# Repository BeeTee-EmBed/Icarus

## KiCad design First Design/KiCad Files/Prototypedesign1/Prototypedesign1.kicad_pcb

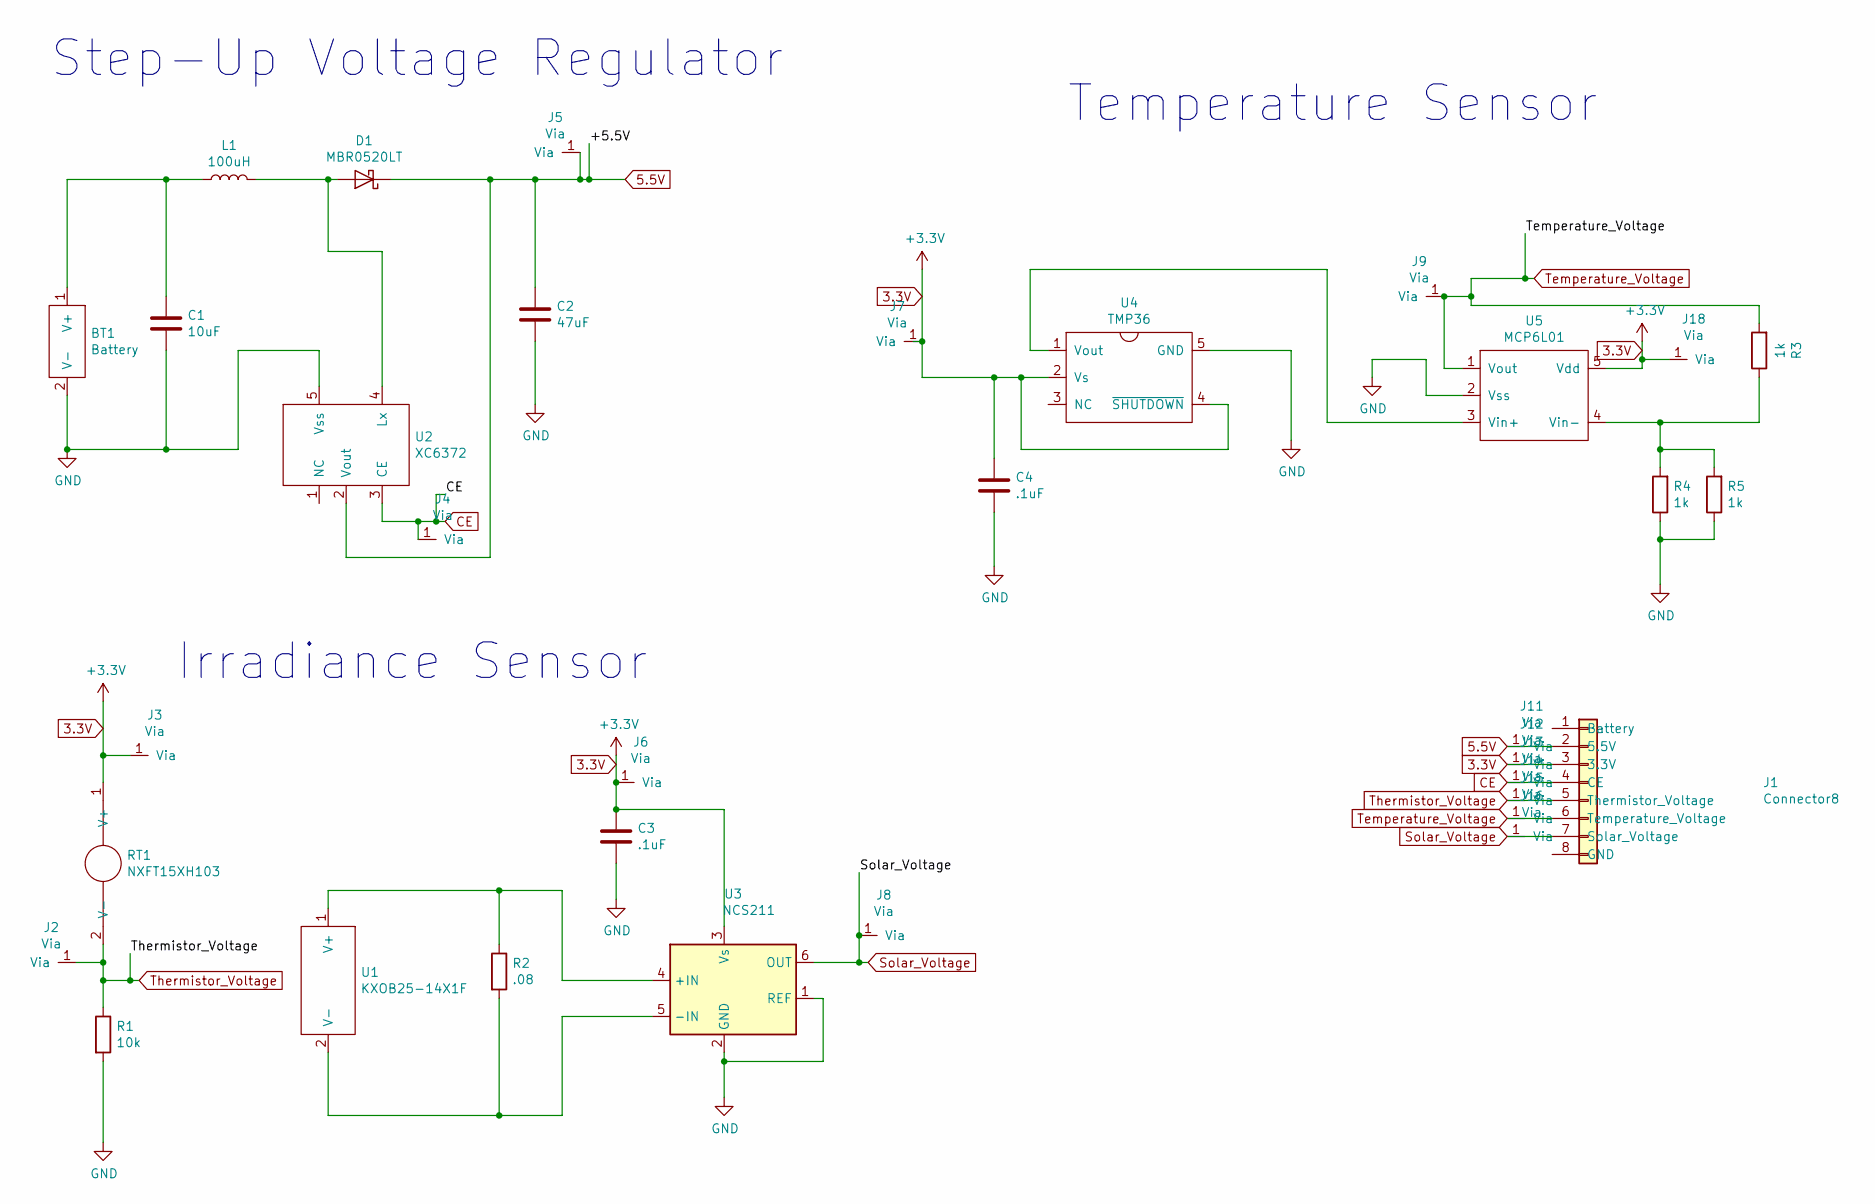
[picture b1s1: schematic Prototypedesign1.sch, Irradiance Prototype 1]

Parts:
BT1: Battery; Prototypebatteryholder
C1: 10uF; C_0603_1608Metric_Pad1.05x0.95mm_HandSolder
C2: 47uF; C_1210_3225Metric_Pad1.42x2.65mm_HandSolder
C3, C4: .1uF; C_0805_2012Metric_Pad1.15x1.40mm_HandSolder
D1: MBR0520LT; D_SOD-123
J1: Connector8; SIP-8
J2, J3, J4, J5, J6, J7, J8, J9, J11, J12, J13, J14, J15, J16, J18: Via
L1: 100uH; Inductor100uH
R1: 10k; R_0805_2012Metric_Pad1.15x1.40mm_HandSolder
R2: .08; R_2512_6332Metric_Pad1.52x3.35mm_HandSolder
R3, R4, R5: 1k; R_0805_2012Metric_Pad1.15x1.40mm_HandSolder
RT1: NXFT15XH103; Thermistor
U1: KXOB25-14X1F; KXOB25
U2: XC6372
U3: NCS211; SOT-363_SC-70-6
U4: TMP36; SOT-23-5_HandSoldering-TMP36
U5: MCP6L01; SOT-23-5_HandSoldering-MCP6L01

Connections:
3.3V: C3.1, C4.1, J1.3 (3.3V), J3.1, J6.1, J7.1, J12.1, J18.1, RT1.1 (V+), U3.3 (Vs), U4.2 (Vs), U4.4 (~SHUTDOWN), U5.5 (Vdd)
5.5V: C2.1, D1.1 (K), J1.2 (5.5V), J5.1, J11.1, U2.2 (Vout)
CE: J1.4 (CE), J4.1, J13.1, U2.3 (CE)
GND: BT1.2 (V-), C1.2, C2.2, C3.2, C4.2, R1.2, R4.1, R5.1, U2.5 (Vss), U3.1 (REF), U3.2 (GND), U4.5 (GND), U5.2 (Vss)
unnamed: BT1.1 (V+), C1.1, L1.1
unnamed: D1.2 (A), L1.2, U2.4 (Lx)
unnamed: R2.1, U1.1 (V+), U3.4 (+IN)
unnamed: R2.2, U1.2 (V-), U3.5 (-IN)
unnamed: R3.1, R4.2, R5.2, U5.4 (Vin-)
unnamed: U4.1 (Vout), U5.3 (Vin+)
Solar_Voltage: J1.7 (Solar_Voltage), J8.1, J16.1, U3.6 (OUT)
Temperature_Voltage: J1.6 (Temperature_Voltage), J9.1, J15.1, R3.2, U5.1 (Vout)
Thermistor_Voltage: J1.5 (Thermistor_Voltage), J2.1, J14.1, R1.1, RT1.2 (V-)

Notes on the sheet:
Step-Up Voltage Regulator
Irradiance Sensor
Temperature Sensor

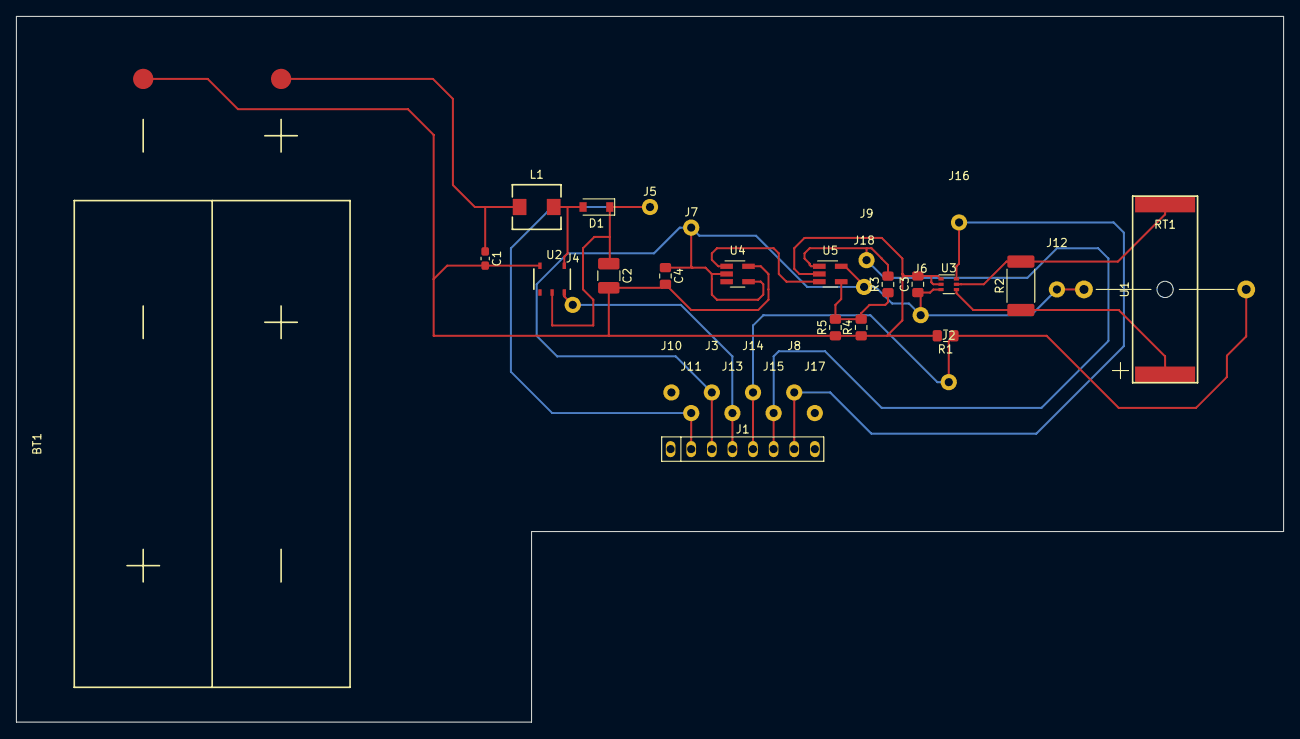
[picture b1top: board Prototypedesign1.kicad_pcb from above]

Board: 2 copper layers, 156.2 x 87.0 mm, 36 parts (0 on the bottom side), 13 nets.

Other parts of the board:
J10, J17: Via

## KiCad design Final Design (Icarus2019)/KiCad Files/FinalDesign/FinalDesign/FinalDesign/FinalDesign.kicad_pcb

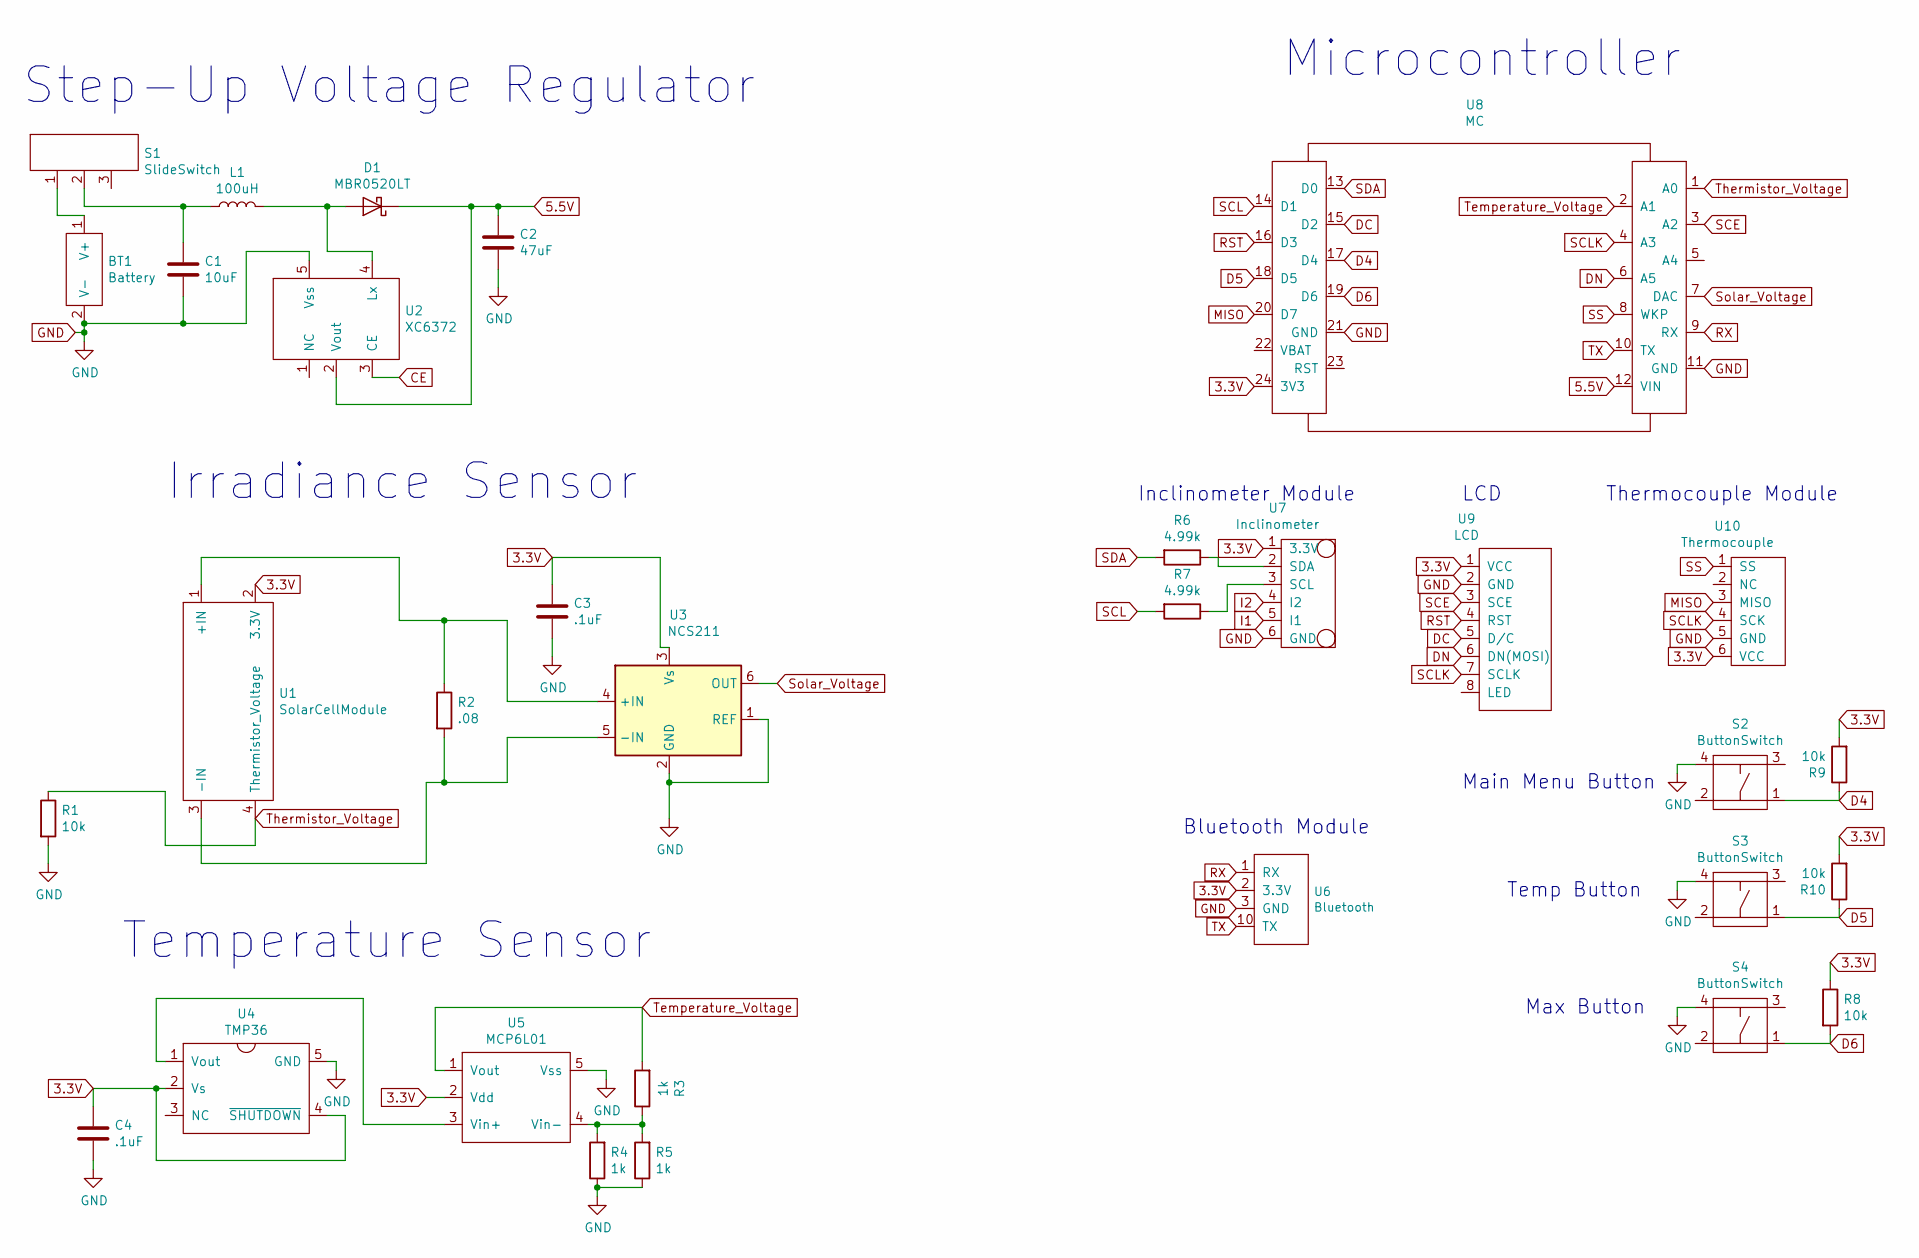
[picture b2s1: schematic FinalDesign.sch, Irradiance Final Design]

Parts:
BT1: Battery; Prototypebatteryholder
C1: 10uF; C_0603_1608Metric_Pad1.05x0.95mm_HandSolder
C2: 47uF; C_1210_3225Metric_Pad1.42x2.65mm_HandSolder
C3, C4: .1uF; C_0805_2012Metric_Pad1.15x1.40mm_HandSolder
D1: MBR0520LT; D_SOD-123
L1: 100uH; Inductor100uH
R1, R8, R9, R10: 10k; R_0805_2012Metric_Pad1.15x1.40mm_HandSolder
R2: .08; R_2512_6332Metric_Pad1.52x3.35mm_HandSolder
R3, R4, R5: 1k; R_0805_2012Metric_Pad1.15x1.40mm_HandSolder
R6, R7: 4.99k; R_0805_2012Metric_Pad1.15x1.40mm_HandSolder
S1: SlideSwitch
S2, S3, S4: ButtonSwitch
U1: SolarCellModule; Solar Cell Module
U2: XC6372
U3: NCS211; SOT-363_SC-70-6
U4: TMP36; SOT-23-5_HandSoldering-TMP36
U5: MCP6L01; SOT-23-5_HandSoldering-MCP6L01
U6: Bluetooth
U7: Inclinometer
U8: MC
U9: LCD
U10: Thermocouple

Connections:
3.3V: C3.1, C4.1, R8.1, R9.2, R10.2, U1.2 (3.3V), U3.3 (Vs), U4.2 (Vs), U4.4 (~SHUTDOWN), U5.2 (Vdd), U6.2 (3.3V), U7.1 (3.3V), U8.24 (3V3), U9.1 (VCC), U10.6 (VCC)
5.5V: C2.1, D1.1 (K), U2.2 (Vout), U8.12 (VIN)
CE: U2.3 (CE)
D4: R9.1, S2.1, U8.17 (D4)
D5: R10.1, S3.1, U8.18 (D5)
D6: R8.2, S4.1, U8.19 (D6)
DC: U8.15 (D2), U9.5 (D/C)
DN: U8.6 (A5), U9.6 (DN(MOSI))
GND: BT1.2 (V-), C1.2, C2.2, C3.2, C4.2, R1.2, R4.1, R5.1, S2.4, S3.4, S4.4, U2.5 (Vss), U3.1 (REF), U3.2 (GND), U4.5 (GND), U5.5 (Vss), U6.3 (GND), U7.6 (GND), U8.11 (GND), U8.21 (GND), U9.2 (GND), U10.5 (GND)
I1: U7.5 (I1)
I2: U7.4 (I2)
MISO: U8.20 (D7), U10.3 (MISO)
unnamed: BT1.1 (V+), S1.1
unnamed: C1.1, L1.1, S1.2
unnamed: D1.2 (A), L1.2, U2.4 (Lx)
unnamed: R2.1, U1.1 (+IN), U3.4 (+IN)
unnamed: R2.2, U1.3 (-IN), U3.5 (-IN)
unnamed: R3.1, R4.2, R5.2, U5.4 (Vin-)
unnamed: R6.1, U7.2 (SDA)
unnamed: R7.1, U7.3 (SCL)
unnamed: U4.1 (Vout), U5.3 (Vin+)
RST: U8.16 (D3), U9.4 (RST)
RX: U6.1 (RX), U8.9 (RX)
SCE: U8.3 (A2), U9.3 (SCE)
SCL: R7.2, U8.14 (D1)
SCLK: U8.4 (A3), U9.7 (SCLK), U10.4 (SCK)
SDA: R6.2, U8.13 (D0)
SS: U8.8 (WKP), U10.1 (SS)
Solar_Voltage: U3.6 (OUT), U8.7 (DAC)
TX: U6.10 (TX), U8.10 (TX)
Temperature_Voltage: R3.2, U5.1 (Vout), U8.2 (A1)
Thermistor_Voltage: R1.1, U1.4 (Thermistor_Voltage), U8.1 (A0)

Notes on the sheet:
Step-Up Voltage Regulator
Temperature Sensor
Irradiance Sensor
Main Menu Button
Temp Button
Max Button
Bluetooth Module
Thermocouple Module
LCD
Microcontroller
Inclinometer Module

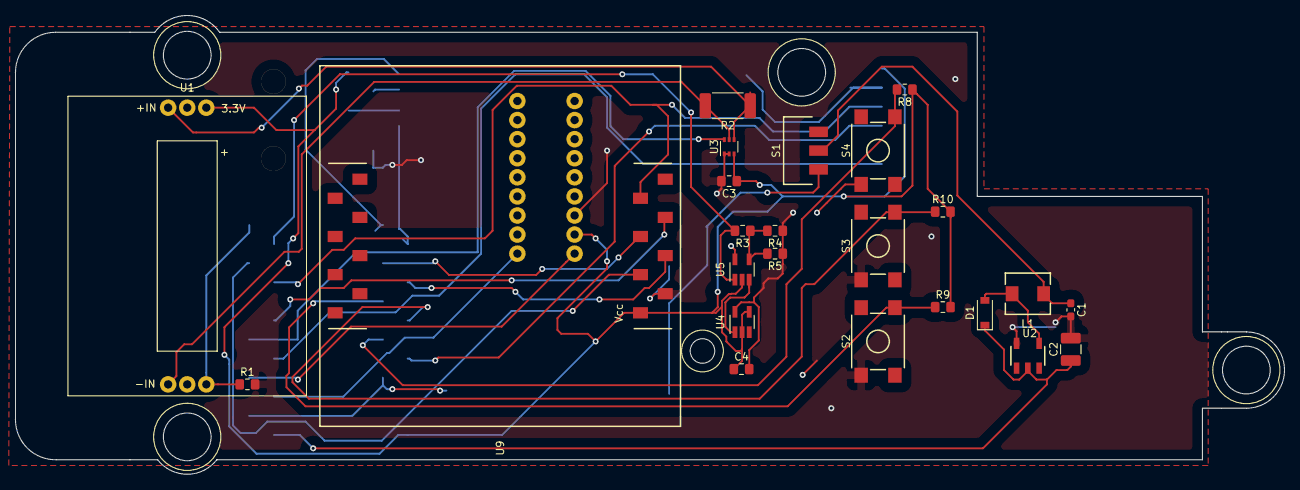
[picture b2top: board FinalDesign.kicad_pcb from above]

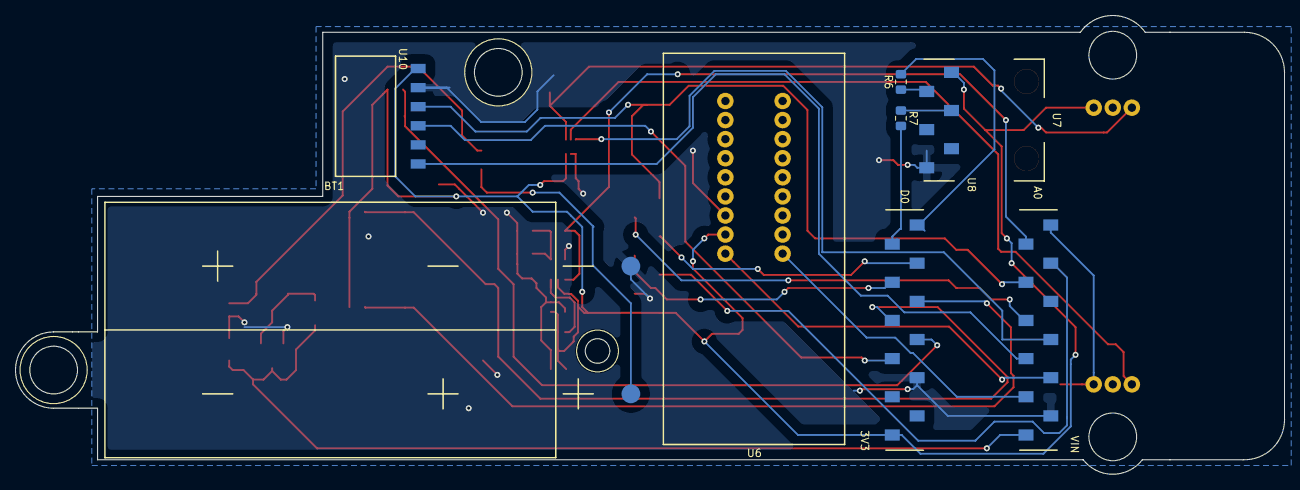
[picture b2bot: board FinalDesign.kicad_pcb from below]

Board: 2 copper layers, 168.9 x 61.1 mm, 31 parts (7 on the bottom side), 29 nets.

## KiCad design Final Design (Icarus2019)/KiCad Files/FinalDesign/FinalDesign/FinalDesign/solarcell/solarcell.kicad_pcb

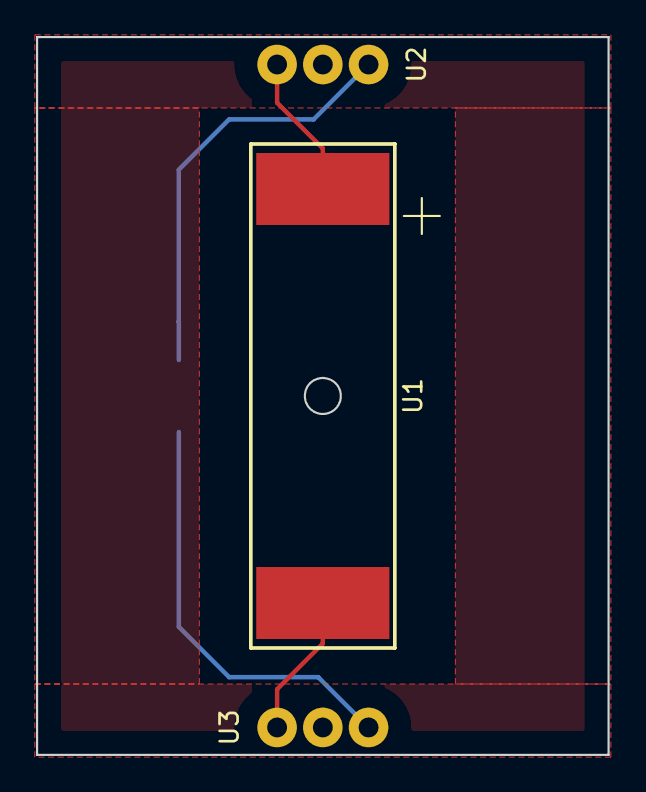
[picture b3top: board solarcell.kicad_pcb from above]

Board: 2 copper layers, 31.8 x 39.9 mm, 4 parts (1 on the bottom side), 4 nets.

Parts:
RT1: NXFT15XH103; Thermistor2
U1: KXOB25-14X1F; KXOB25
U2, U3: 3pin

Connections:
3.3V: RT1.1, U2.1
+IN: U1.1, U2.3
-IN: U1.2, U3.1
Thermistor_Voltage: RT1.2, U3.3

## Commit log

2019-07-30 Simplified the getThermistorVoltage function
2019-07-31 Add the main file
2019-08-02 Modified the bit shift in the short circuit function
2019-08-02 Added a rolling average for the solar cell voltage, to smooth irradiance readings
2019-08-05 Modified sampling rate to speed up rolling median filter response
2019-08-05 Fixing delay time for sampling speed
2019-08-09 Altered number of places for irradiance, incline, and ambient temp to account for sensor precision
2019-08-13 Altered setScreen to use enum and switch, replacing if/then statments for the sake of clarity
2019-08-13 Simplified findMax function to use a loop to display text, and truncated display values to ones place
2019-08-13 Replaced magic numbers with const variables, and reordered global variables for the sake of clarity
2019-08-13 magic number variable replacement, and adding degree's sign to output to display
2019-08-13 altered setScreen outputs to add C after degrees symbol
2019-08-13 added degree symbol to output after measurements are displayed
2019-08-13 Changed some global variable types to static const
2019-08-13 removed wifi function, simplified comments to account for coding standard
2019-08-13 Unbroke my code, due to accidental line deletion of updating display
2019-08-13 Changed const variables to upper case to match coding standards
2019-08-13 altering code and testing to chekc smapling data rates
2019-08-13 Changed code to adhere to coding standards
2019-08-14 Changed Degrees to angle
2019-08-15 Added calibration offset
2019-08-15 Adding back file after moving
2019-08-19 Modified SMA filter to not use median and not sort array each cycle
2019-08-20 Converted irradiance measurement to luminosity measurement to test UV-A lamp
2019-08-20 Adding all network files
2019-08-23 Added a zero-ing equation for the accelerometer object, to make the initial starting plane the zero degree plane
2019-08-29 Chaznged comment formats to adhere to coding standards including to-do, and changed equation to use calibration offset variable, not a magic number
2019-08-29 Changed comments for coding standard
